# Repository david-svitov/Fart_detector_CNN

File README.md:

# Fart Detector
Схемы, исходный код и нейросетевые модели для создания детектора пердежа.

Видео о детекторе: https://youtu.be/zE5qQ1LDb7s

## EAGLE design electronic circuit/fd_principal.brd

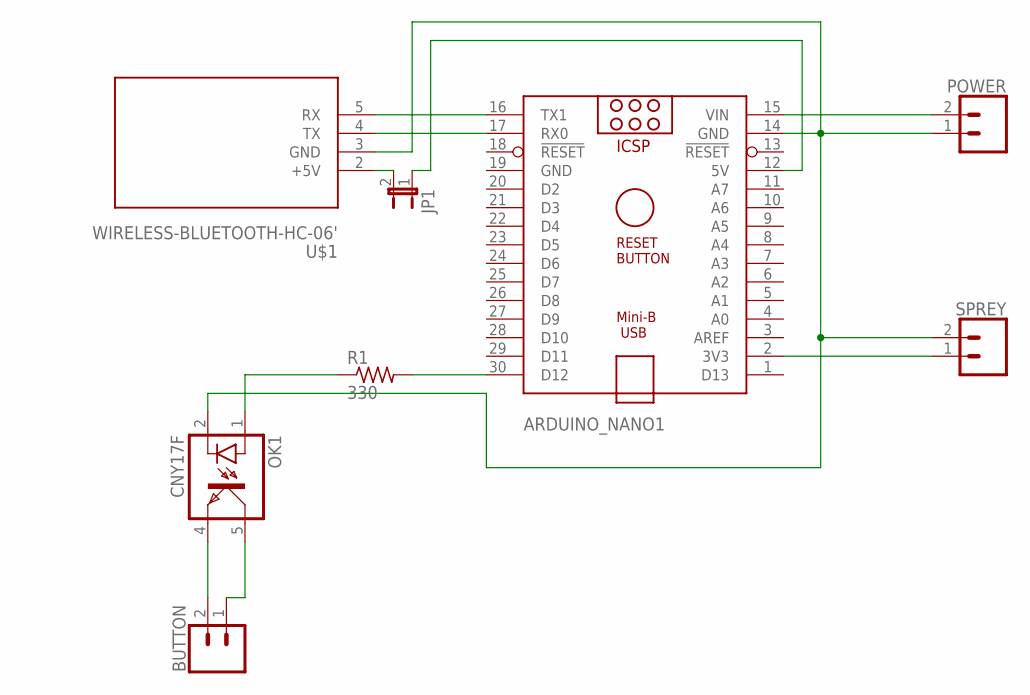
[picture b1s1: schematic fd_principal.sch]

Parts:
ARDUINO_NANO1: ARDUINO_NANO
BUTTON: CONN_025MM; SCREWTERMINAL-5MM-2
JP1: JP1E; JP1
OK1: CNY17F; DIL06
POWER: CONN_025MM; SCREWTERMINAL-5MM-2
R1: 330; 0207/10
SPREY: CONN_025MM; SCREWTERMINAL-5MM-2
U$1: WIRELESS-BLUETOOTH-HC-06'; WIRELESS-BLUETOOTH-HC-06

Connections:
GND: ARDUINO_NANO1.19 (GND)
unnamed: ARDUINO_NANO1.15 (VIN), POWER.2
unnamed: ARDUINO_NANO1.14 (GND), OK1.2 (C), POWER.1, SPREY.2, U$1.3 (GND)
unnamed: ARDUINO_NANO1.16 (TX1), U$1.5 (RX)
unnamed: ARDUINO_NANO1.17 (RX0), U$1.4 (TX)
unnamed: ARDUINO_NANO1.30 (D12), R1.2
unnamed: OK1.1 (A), R1.1
unnamed: BUTTON.2, OK1.4 (EMIT)
unnamed: BUTTON.1, OK1.5 (COL)
unnamed: ARDUINO_NANO1.2 (3V3), SPREY.1
unnamed: JP1.2, U$1.2 (+5V)
unnamed: ARDUINO_NANO1.12 (5V), JP1.1

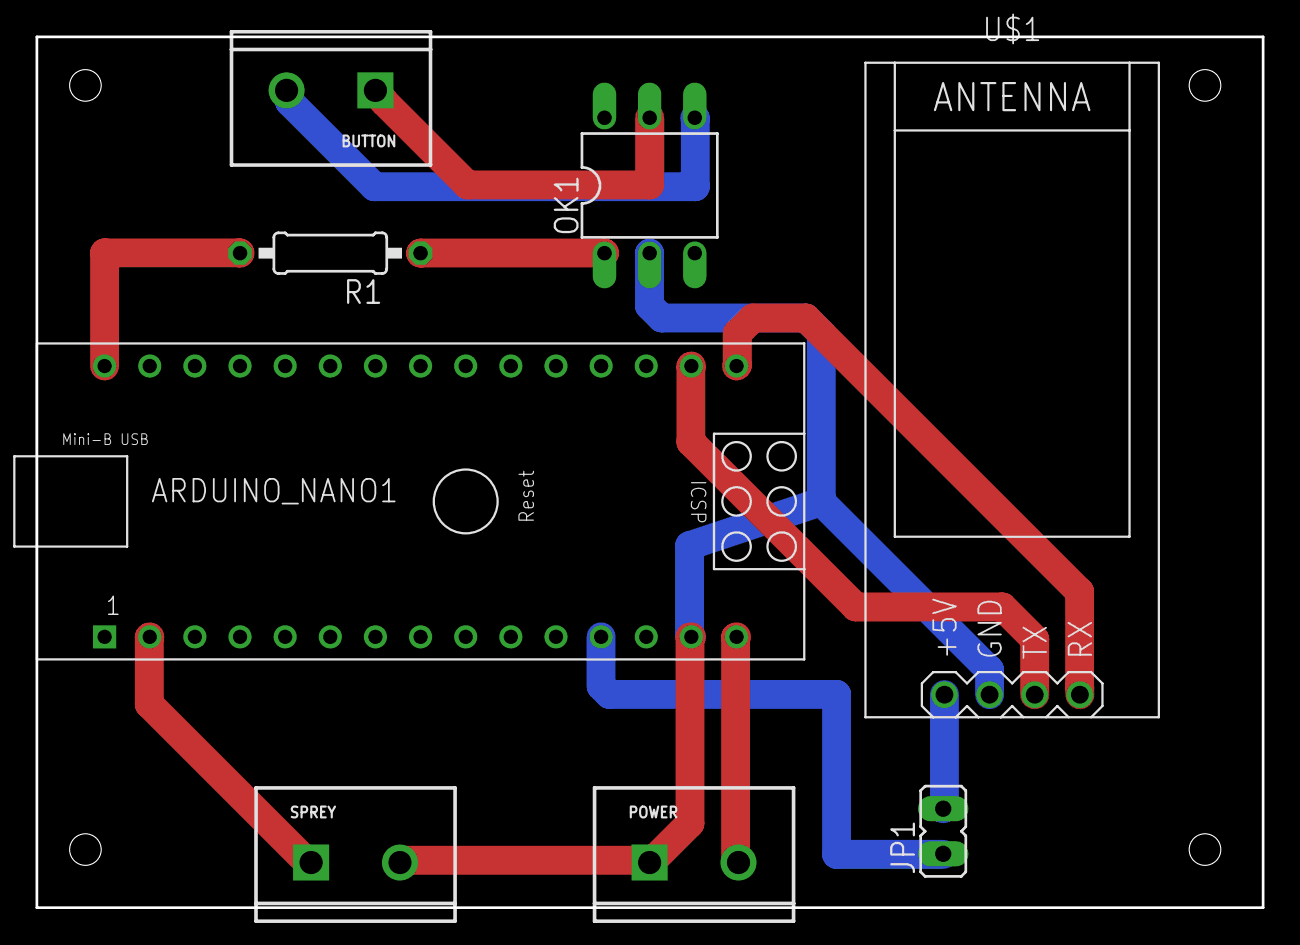
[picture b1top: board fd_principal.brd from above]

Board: 2 copper layers, 69.0 x 49.0 mm, 8 parts (0 on the bottom side), 11 nets.

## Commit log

2021-10-05 All project files
2021-10-05 Modify readme

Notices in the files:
parts and their libraries:
SparkFun-Connectors: Licensing: Creative Commons ShareAlike 4.0 International - https://creativecommons.org/licenses/by-sa/4.0
diy-modules: Released under the Creative Commons Attribution 4.0 International License: http://creativecommons.org/licenses/by/4.0
